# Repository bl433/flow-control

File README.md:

# flow-control
Solenoid valve manager with PWM-styled energizing, master control, and possible flow rate feedback.
- Nozzle sizes are 3/4", meant for standard purpose garden hoses.
- Intended to be powered by a 12V 2A power supply.
- Solenoids are connected to the bottom of the valve manager through a 2-pin socket.

<b>This repository is intended for the NJIT ECET-430 course.</b>

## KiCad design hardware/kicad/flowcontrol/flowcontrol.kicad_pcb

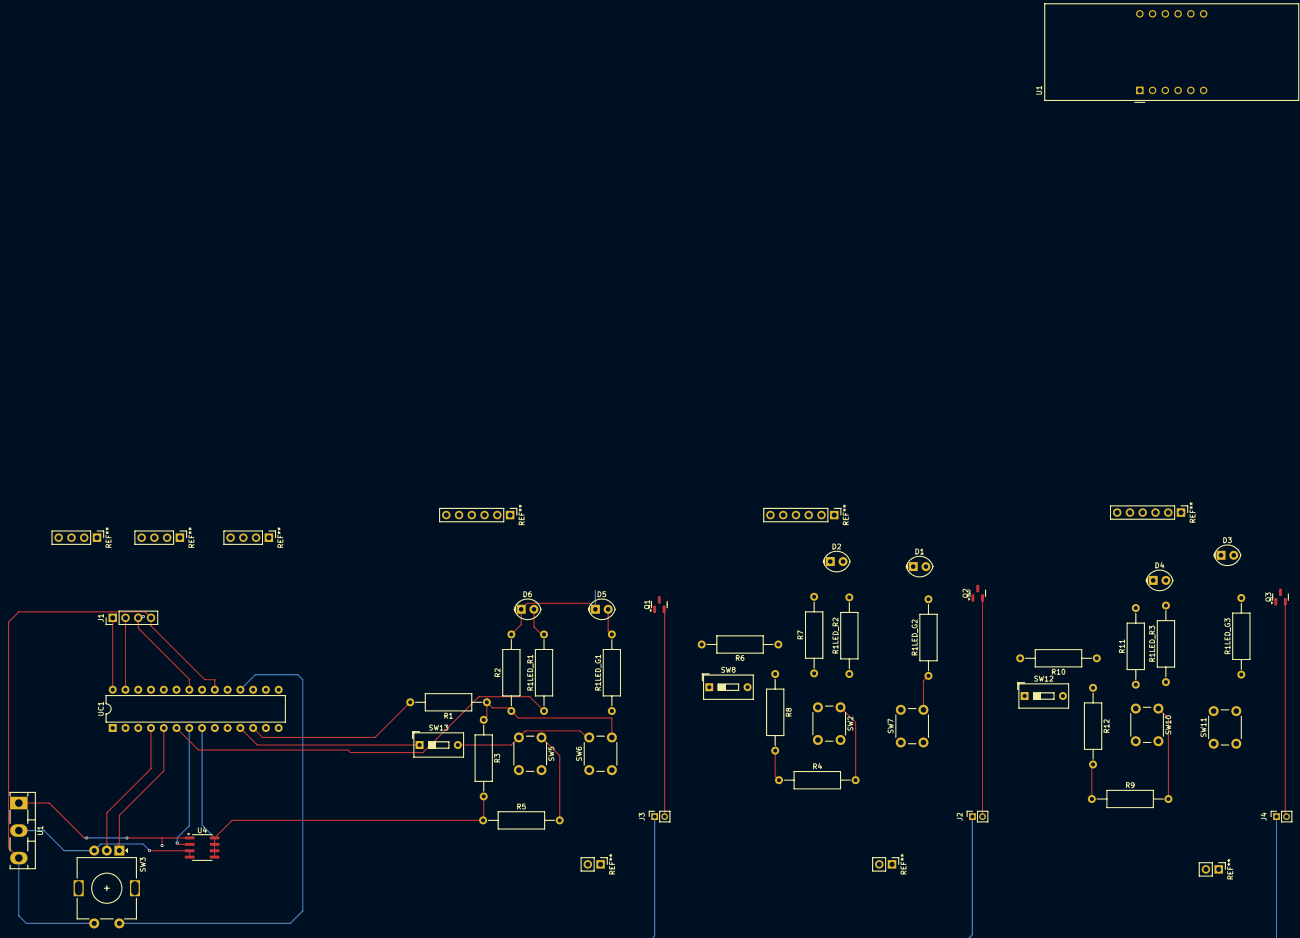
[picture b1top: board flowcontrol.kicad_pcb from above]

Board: 2 copper layers, 45 parts (0 on the bottom side), 33 nets.

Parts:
D1, D3, D5: SOL1_GRN; LED_Oval_W5.2mm_H3.8mm
D2, D4, D6: SOL1_RED; LED_Oval_W5.2mm_H3.8mm
J1: 4-digit I2C Display; PinHeader_1x04_P2.54mm_Vertical
J2, J3, J4: SOL1_PORT; PinSocket_1x02_P2.00mm_Vertical
Q1, Q2, Q3: SOL1_NFET; SOT-23
R1, R6, R10: 100O; R_Axial_DIN0309_L9.0mm_D3.2mm_P15.24mm_Horizontal
R1LED_G1, R1LED_G2, R1LED_G3: 220; R_Axial_DIN0309_L9.0mm_D3.2mm_P15.24mm_Horizontal
R1LED_R1, R1LED_R2, R1LED_R3: R; R_Axial_DIN0309_L9.0mm_D3.2mm_P15.24mm_Horizontal
R2, R4, R5, R7, R9, R11: 1kO; R_Axial_DIN0309_L9.0mm_D3.2mm_P15.24mm_Horizontal
R3, R8, R12: 100; R_Axial_DIN0309_L9.0mm_D3.2mm_P15.24mm_Horizontal
SW2, SW5, SW10: BUTTON_CONFIG; SW_PUSH_6mm_mod
SW3: DIAL; RotaryEncoder_Vertical_H20mm
SW6, SW7, SW11: BUTTON_FORCE; SW_PUSH_6mm_mod
SW8, SW12, SW13: SWITCH_MAIN; SW_DIP_SPSTx01_Slide_9.78x4.72mm_W7.62mm_P2.54mm
U1: SOL1_DISP; CA56-12SRWA
U1#2: 5V Regulator; TO-218-3_Vertical
U4: XL1509-3.3; SOIC-8_3.9x4.9mm_P1.27mm
UC1: ATmega328-P; DIP-28_W7.62mm

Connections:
/Input Display/12V_R: J2.1, J3.1, J4.1, U1#2.1 (IN), U4.1 (VIN)
/Input Display/CLOCK: SW3.C, UC1.4 (PD2)
/Input Display/DT: SW3.A, UC1.5 (PD3)
/Input Display/SCL: J1.1, UC1.28 (PC5)
/Input Display/SDA: J1.2, UC1.27 (PC4)
/Input Display/SWITCH: SW3.S2, UC1.18 (PB4)
/Input Display/VCC_E: J1.4, SW2.4, SW3.S1, SW5.4, SW6.1, SW7.1, SW8.2 (B), SW10.4, SW11.1, SW12.2 (B), SW13.2 (B), U1#2.3 (OUT), UC1.20 (AVCC)
/Microcontroller/SOL1_MAIN: SW13.1 (A), UC1.11 (PD5)
/Microcontroller/SOL1_OUT: R1.2, UC1.12 (PD6)
/Microcontroller/SOL1_SEL: R5.2, SW5.3, UC1.13 (PD7)
/Microcontroller/SOL1_WAIT: R1LED_R1.1, UC1.6 (PD4)
/Microcontroller/SOL2_MAIN: SW8.1 (A), UC1.14 (PB0)
/Microcontroller/SOL2_OUT: R6.2, UC1.15 (PB1)
/Microcontroller/SOL2_SEL: R4.2, SW2.3, UC1.17 (PB3)
/Microcontroller/SOL2_WAIT: R1LED_R2.1, UC1.16 (PB2)
/Microcontroller/SOL3_MAIN: SW12.1 (A), UC1.23 (PC0)
/Microcontroller/SOL3_OUT: R10.2, UC1.24 (PC1)
/Microcontroller/SOL3_SEL: R9.2, SW10.3, UC1.26 (PC3)
/Microcontroller/SOL3_WAIT: R1LED_R3.1, UC1.25 (PC2)
GND: D1.1 (K), D2.1 (K), D3.1 (K), D4.1 (K), D5.1 (K), D6.1 (K), J1.3, Q1.1 (D), Q1.3 (G), Q2.1 (D), Q2.3 (G), Q3.1 (D), Q3.3 (G), R2.2, R3.2, R4.1, R5.1, R7.2, R8.2, R9.1, R11.2, R12.2, SW3.B, U1#2.2 (GND), U4.3 (FB), U4.4 (~EN), U4.5 (GND), U4.6 (GND), U4.7 (GND), U4.8 (GND), UC1.8 (GND), UC1.22 (GND)
unnamed: D1.2 (A), R1LED_G2.2
unnamed: D2.2 (A), R1LED_R2.2
unnamed: D3.2 (A), R1LED_G3.2
unnamed: D4.2 (A), R1LED_R3.2
unnamed: D5.2 (A), R1LED_G1.2
unnamed: D6.2 (A), R1LED_R1.2
unnamed: J2.2, Q2.2 (S)
unnamed: J3.2, Q1.2 (S)
unnamed: J4.2, Q3.2 (S)
unnamed: R1.1, R1LED_G1.1, R2.1, R3.1, SW6.2
unnamed: R1LED_G2.1, R6.1, R7.1, R8.1, SW7.2
unnamed: R1LED_G3.1, R10.1, R11.1, R12.1, SW11.2
unnamed: U4.2 (OUT), UC1.7 (VCC)

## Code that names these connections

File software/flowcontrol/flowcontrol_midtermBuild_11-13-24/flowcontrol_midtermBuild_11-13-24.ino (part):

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#define ENC_B 3
#define ENC_SW 1
// MAIN - Main decision switch. Solenoid will not flow or count down if not receiving 5v. (off)
#define SOL1_MAIN 4
// OUT - Output valve control. Linked to the green LED.
#define SOL1_OUT 5
// WAIT - Hold visual. Linked to the red LED.
#define SOL1_WAIT 6
// SW_SEL - Pushbutton to select solenoid for configuration. Push once for Delay, push twice for Duration.
#define SOL1_SW_SEL 7
// SW_FORCE - Pushbutton to forcefully enable SOL1_OUT. This doesn't even need to exist and can be linked to a 5V.
//#define SOL1_SW_FORCE 11
#define SOL2_MAIN 8
#define SOL2_OUT 9
#define SOL2_WAIT 10
#define SOL2_SW_SEL 11
// It's impossible to expand to the fourth solenoid with the current microcontroller unless there's a way to expand the pins.
// We COULD squeeze one, pins 14, 15, 16, 17 for SOL3. Not SOL4 though. Three might as well be our absolute maximum.
// There are ways. An 8-pin expansion board would be ideal for this matter, but ends up relying on I2C communications, SDA, and SCL.
#define SOL3_MAIN 14
#define SOL3_OUT 15
#define SOL3_WAIT 16
#define SOL3_SW_SEL 17

#define HOUR_CONVERT 60
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  pinMode(ENC_A, INPUT_PULLUP);
  pinMode(ENC_B, INPUT_PULLUP);
  pinMode(ENC_SW, INPUT);
  pinMode(SOL1_OUT, OUTPUT);
  pinMode(SOL1_WAIT, OUTPUT);
  attachInterrupt(digitalPinToInterrupt(ENC_A), read_encoder, CHANGE);
  attachInterrupt(digitalPinToInterrupt(ENC_B), read_encoder, CHANGE);

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
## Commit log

2024-09-03 Created logbook
2024-09-04 desktop app organization
    the github directory can now be edited from a laptop using a desktop app.
2024-09-04 inclusion of hardware and software files
    they don't show up unless I populate it.
2024-09-05 Create LICENSE
2024-09-05 Create .gitignore, kicad template
2024-09-05 Create Tools and Software.txt
    To present a proof of concept.
2024-09-10 documentation updates
2024-09-12 september 12th
    Updated logs from September 10th
    Updated logs from September 12th
    Decided to integrate Arduino.
2024-09-16 parts list addition
    A lot of this have already been ordered. This is subject to expand.
2024-09-16 replace block diagram
    added revision 2, featuring two sample lanes and two encoder module knobs per lane
2024-09-19 prepared kicad and arduino files
    Both files are very rudimentary. We'll eventually add psuedocode and fiddle with the components in the schematic so that we'll make these files proper.
2024-09-19 re-added log book
    not sure why it disappeared
2024-09-23 updated kicad file
    connected most devices together through labels.
    still requires LCD I2C modules or 4-digit schematic blocks.
2024-09-23 update README.md
    Also made the repository public because nobody, not even the professor can't see it.
    As a result, a bolded disclaimer that this is meant for college will be provided.
2024-10-02 KiCad Sectioning
    Turned the schematic into multiple sections - microcontroller, inputs, outputs, and display as the core blocks.
2024-10-14 Create Tests
    Tests that we might need to do to ensure the project works
2024-10-15 Added requested test procedures
    Four ideal test protocols have been added:
    - Power-up sanity check
    - Manual activation
    - Small-scale interval
    - Individual settings
2024-10-30 Schemiatic update
2024-11-14 Added Arduino coding
2024-11-14 Added Visio flowchart files
2024-12-19 major code additions
2024-12-19 final code for the final presentation on 12/19
2024-12-19 Updated KiCad schematic to final rendition
2024-12-19 labeled the old pcb old
2024-12-21 semi-final updates for the report
2024-12-23 finalized updates for the individual reports
    For the sake up uploading the ECET-430 final report before midnight. My variant is flowcontrol_BL, since you worked on the wiring as well.
2024-12-23 Gerber, Drill, and Bill of Materials generation
